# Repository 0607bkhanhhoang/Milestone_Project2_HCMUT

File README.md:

Aquarium Monitoring System Datalogger
Overview
Welcome to the Aquarium Monitoring System Datalogger project! This system is designed to help aquarium enthusiasts and professionals maintain optimal conditions for their aquatic environments by continuously monitoring and logging key parameters.

Features
Real-time Monitoring: Continuously tracks essential water parameters such as temperature, pH, salinity, and dissolved oxygen.
Data Logging: Stores historical data for analysis, helping you identify trends and make informed decisions about your aquarium’s health.
Alerts and Notifications: Sends alerts via email or SMS if any parameter goes out of the safe range, allowing for prompt corrective actions.
User-friendly Interface: Provides a web-based dashboard where users can view real-time data, historical trends, and system status.
Automation Capabilities: Integrates with other smart devices to automate tasks like feeding, lighting, and water changes based on the monitored data.
Components
Sensors: High-precision sensors for measuring temperature, pH, salinity, and dissolved oxygen.
Microcontroller: A microcontroller (e.g., Arduino or Raspberry Pi) to collect data from sensors and send it to the cloud.
Cloud Storage: Secure cloud storage for logging data and providing access from anywhere.
Dashboard: A web-based dashboard built with modern web technologies for data visualization and system management.
Getting Started
Clone the Repository:
git clone https://github.com/yourusername/aquarium-monitoring-system.git
cd aquarium-monitoring-system

Install Dependencies: Follow the instructions in the INSTALL.md file to set up the necessary software and hardware components.
Configure the System: Update the configuration files with your specific settings, such as sensor calibration values and alert thresholds.
Run the System: Start the monitoring system by running the main script:
python main.py

Contributing
We welcome contributions from the community! Please read our CONTRIBUTING.md file for guidelines on how to contribute to this project.

License
This project is licensed under the MIT License. See the LICENSE file for more details.

Feel free to customize this overview to better fit your specific project and its features! If you need more detailed sections or have any other questions, let me know!

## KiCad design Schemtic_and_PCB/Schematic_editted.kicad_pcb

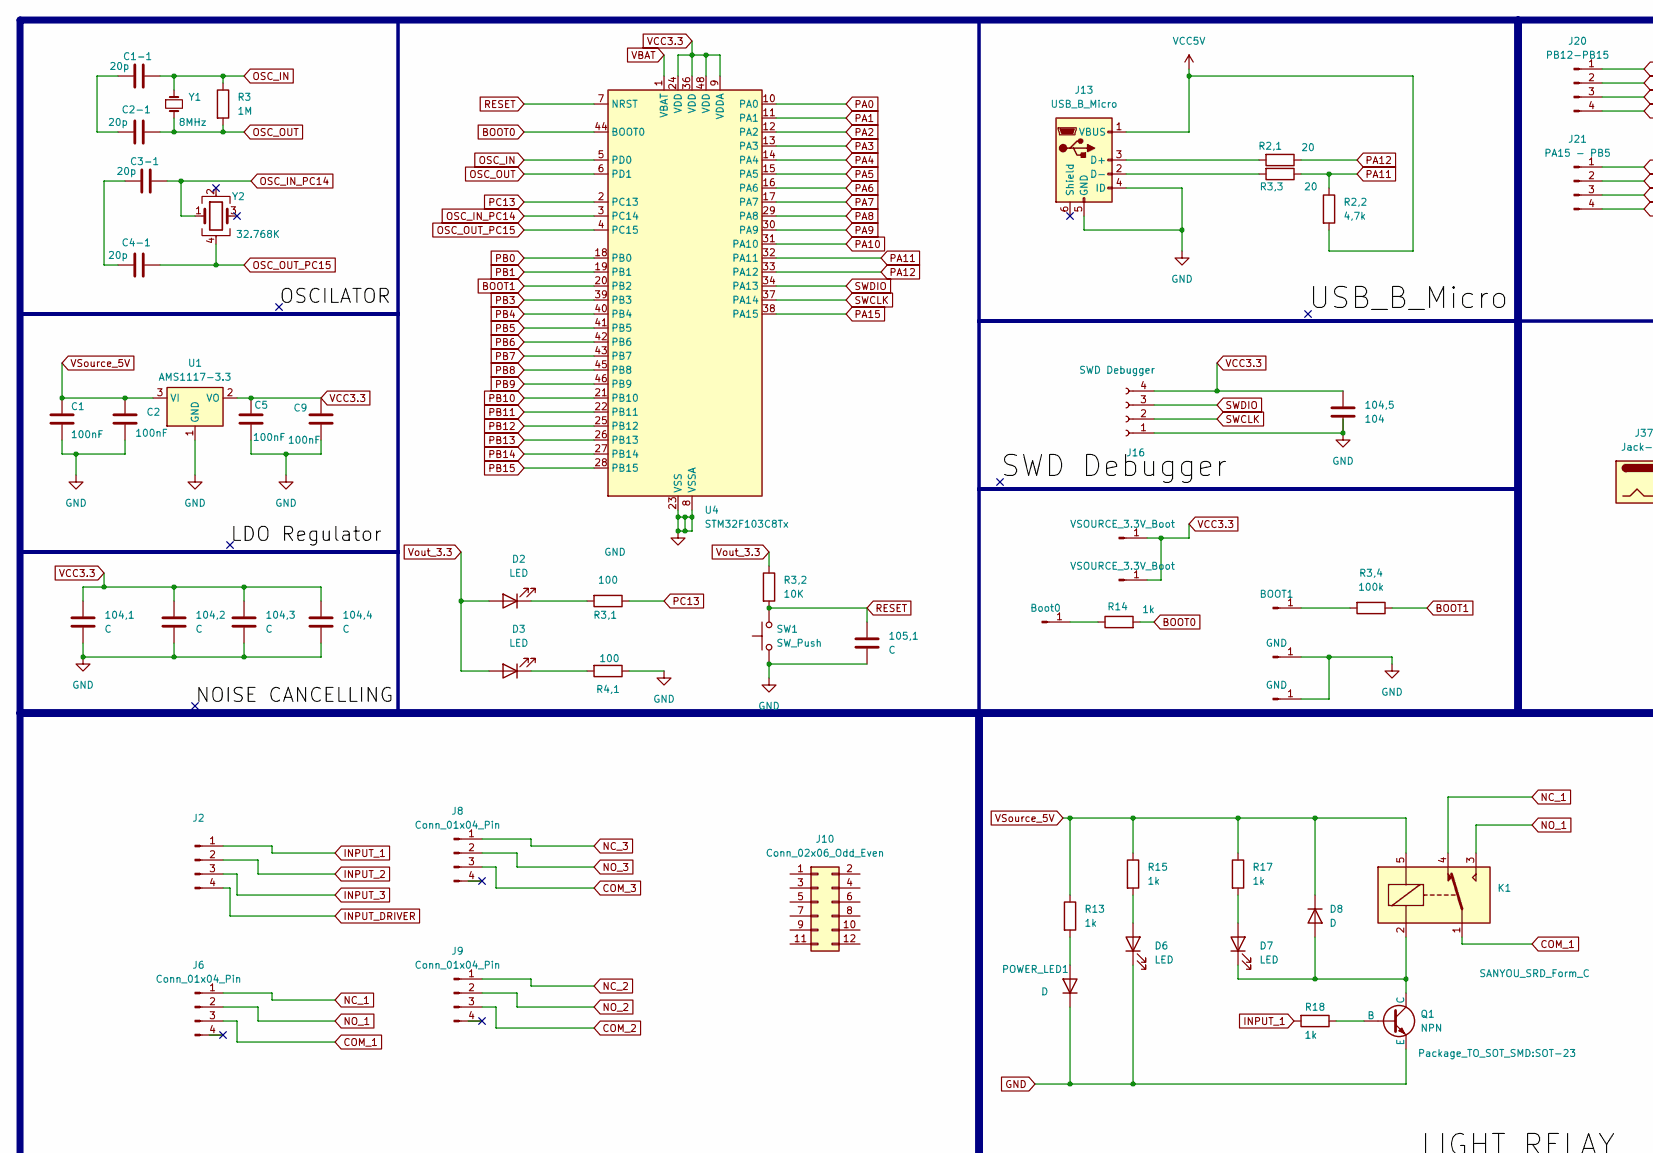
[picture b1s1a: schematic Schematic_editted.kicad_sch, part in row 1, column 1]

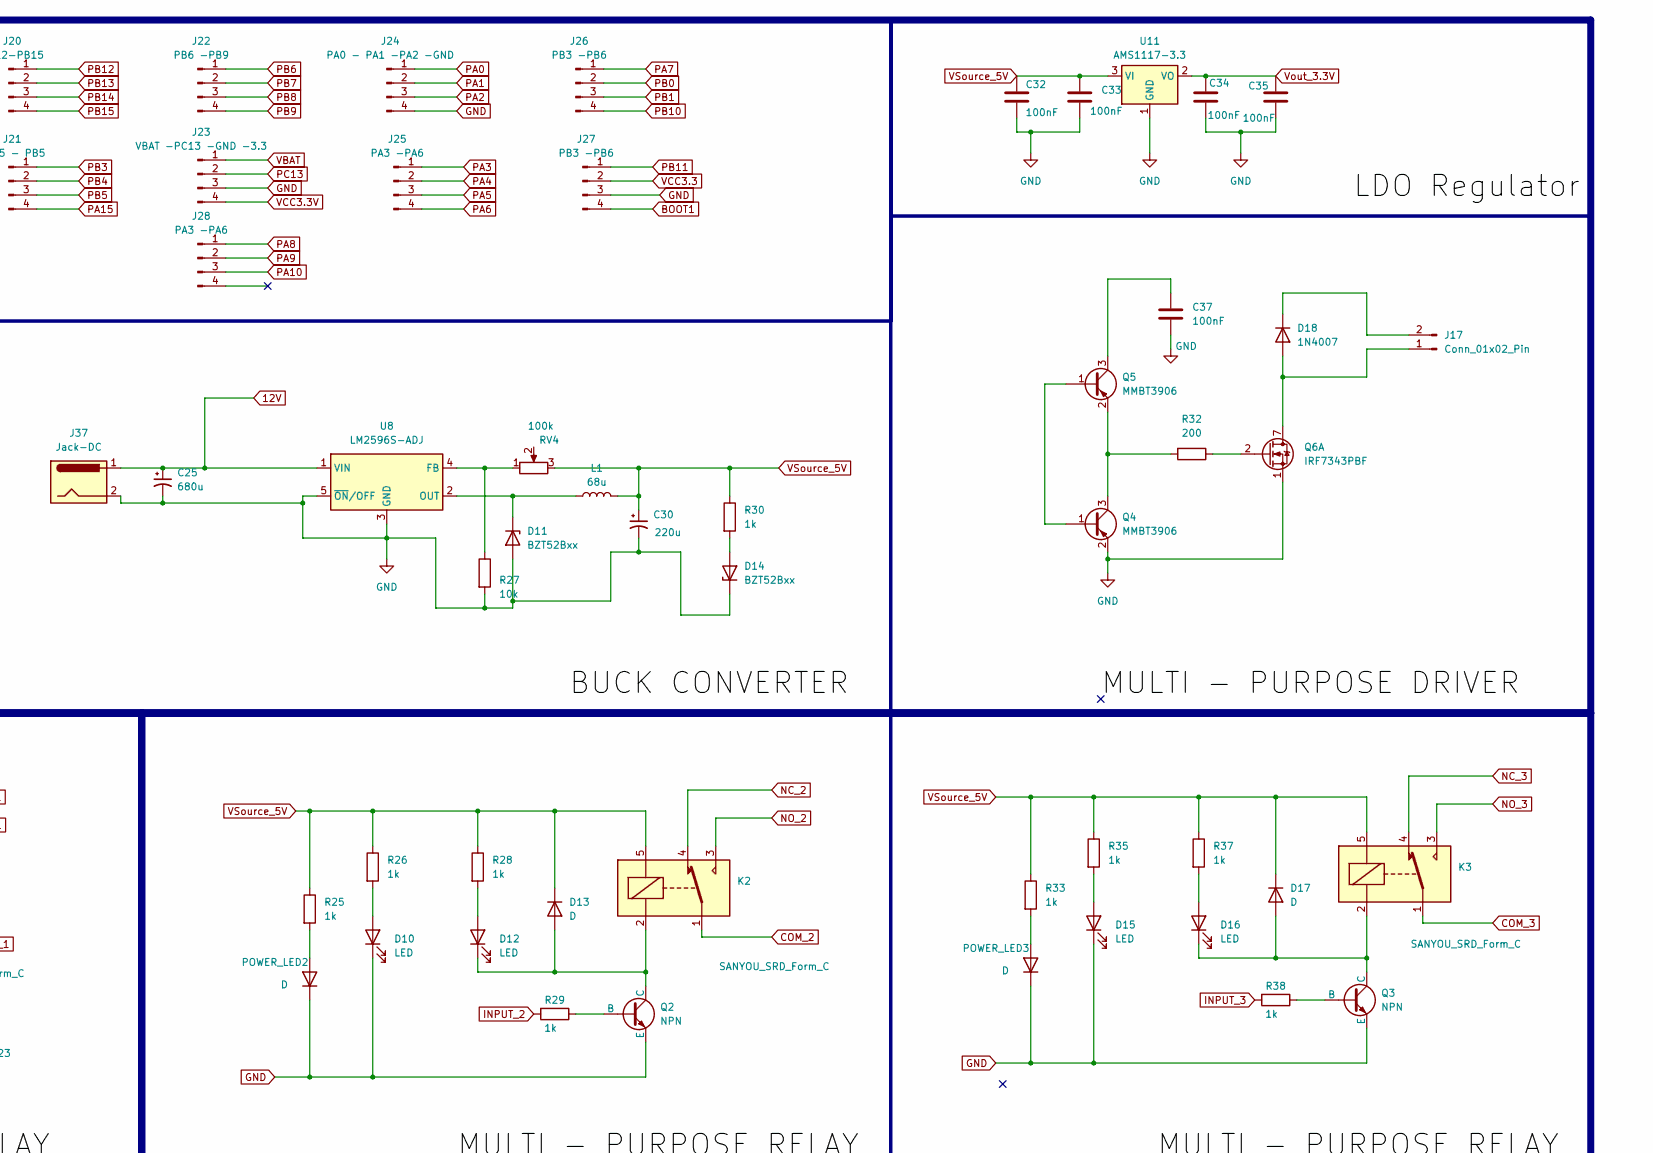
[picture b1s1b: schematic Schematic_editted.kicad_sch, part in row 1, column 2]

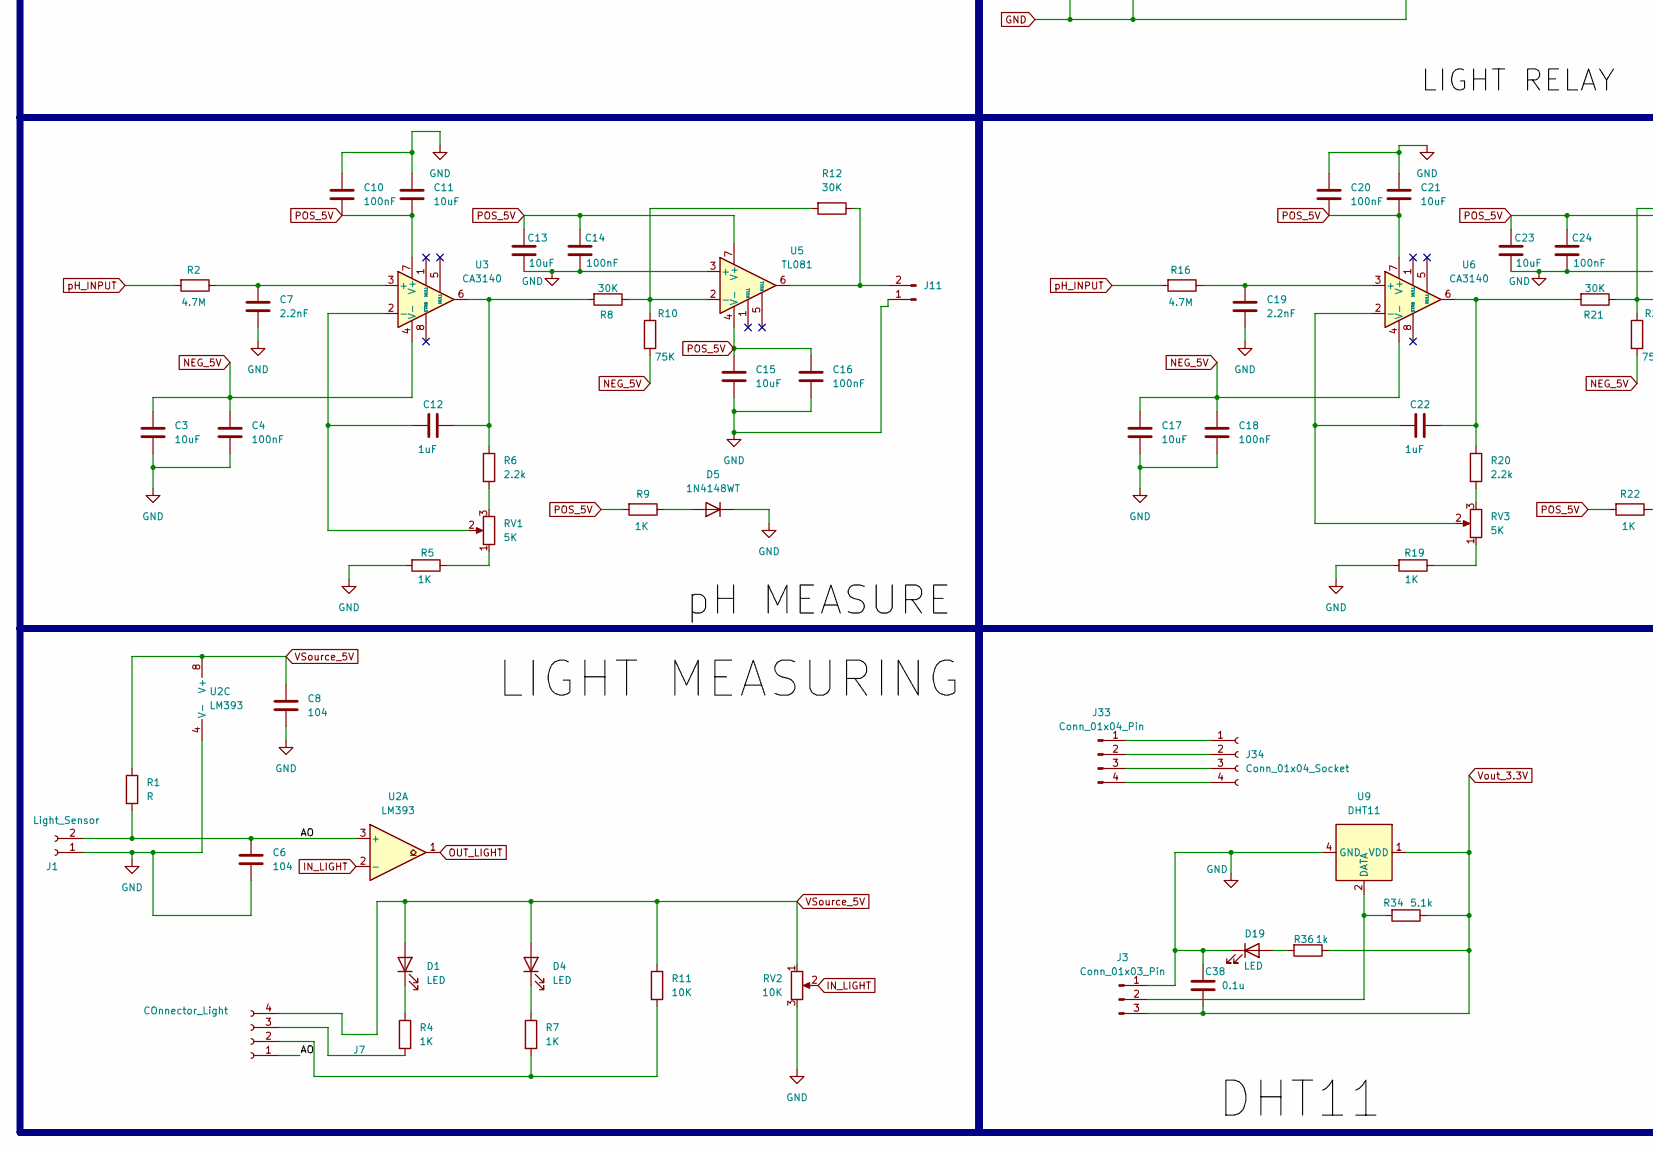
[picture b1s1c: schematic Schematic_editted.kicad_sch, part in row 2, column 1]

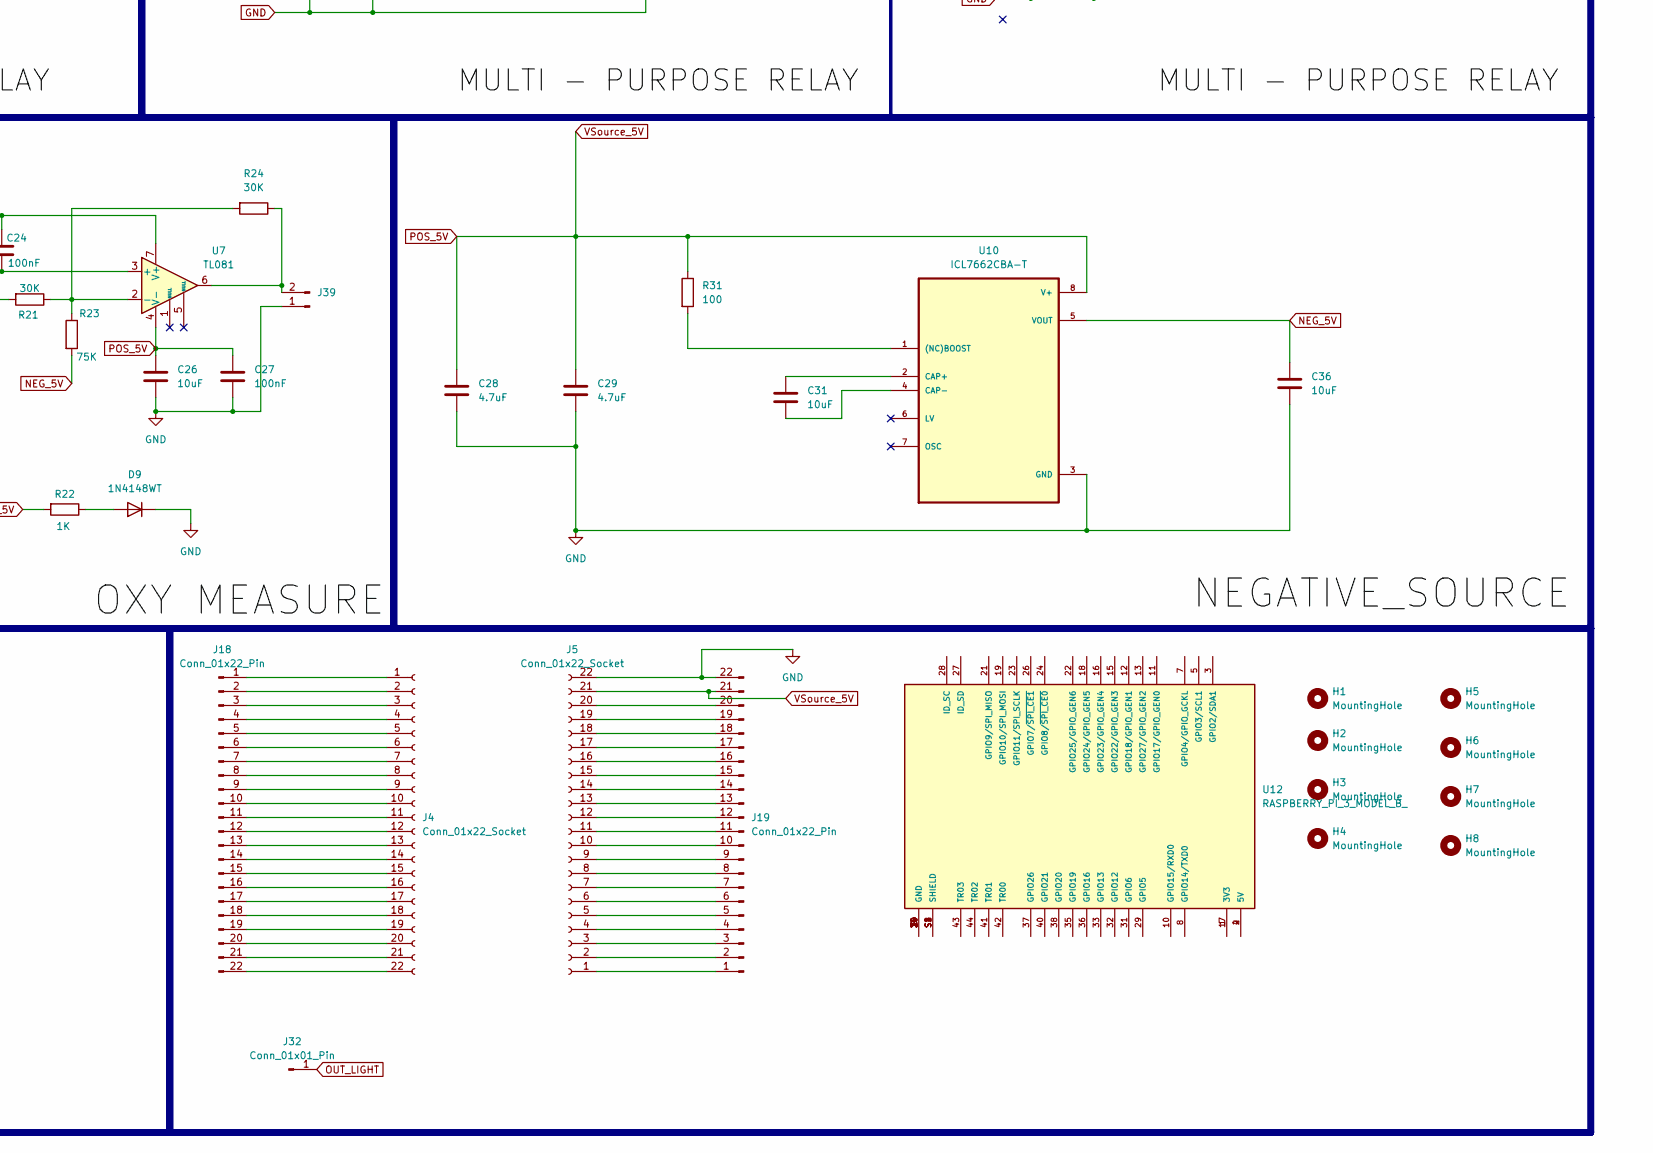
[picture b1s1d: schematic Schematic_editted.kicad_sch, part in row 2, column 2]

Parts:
104,1: C; C_0201_0603Metric
104,2, 105,1: C; C_0603_1608Metric
104,3, 104,4: C; C_0603_1608Metric_Pad1.08x0.95mm_HandSolder
104,5: 104; C_0603_1608Metric
C1, C2, C4, C5, C9, C10, C14, C16, C18, C20, C24, C27, C32, C33, C34, C35, C37: 100nF; C_0603_1608Metric
C1-1, C2-1, C3-1, C4-1: 20p; C_0603_1608Metric
C3, C11, C13, C15, C17, C21, C23, C26, C36: 10uF; C_0603_1608Metric
C6, C8: 104; C_0603_1608Metric
C7, C19: 2.2nF; C_0603_1608Metric
C12, C22: 1uF; C_0603_1608Metric
C25: 680u; CP_Elec_10x10.5
C28: 4.7uF; C_0805_2012Metric_Pad1.18x1.45mm_HandSolder
C29: 4.7uF; C_0805_2012Metric
C30: 220u; CP_Elec_10x10.5
C31: 10uF; C_1206_3216Metric
C38: 0.1u; C_0603_1608Metric
D1, D2: LED; C_0603_1608Metric
D3, D4, D6, D7, D19: LED; LED_0603_1608Metric
D5, D9: 1N4148WT; D_SOD-523
D8: D; LED_0603_1608Metric
D10, D12, D15, D16: LED; LED_0603_1608Metric_Pad1.05x0.95mm_HandSolder
D11, D14: BZT52Bxx; D_SOD-123F
D13, D17: D; LED_0603_1608Metric_Pad1.05x0.95mm_HandSolder
D18: 1N4007; D_DO-41_SOD81_P10.16mm_Horizontal
H1, H2, H3, H4, H5, H6, H7, H8: MountingHole; MountingHole_3.5mm_Pad
J1: Light_Sensor; PinHeader_1x02_P2.00mm_Vertical
J2, J6: Conn_01x04_Pin; PinHeader_1x04_P2.00mm_Vertical_SMD_Pin1Left
J3: Conn_01x03_Pin; PinHeader_1x03_P2.00mm_Vertical
J4, J5: Conn_01x22_Socket; PinHeader_1x22_P2.54mm_Vertical
J7: COnnector_Light; PinSocket_1x05_P2.00mm_Vertical_SMD_Pin1Left
J8, J9: Conn_01x04_Pin; PinSocket_1x05_P2.00mm_Vertical_SMD_Pin1Left
J10: Conn_02x06_Odd_Even
J11, J17, J39: Conn_01x02_Pin; PinHeader_1x02_P2.00mm_Vertical
J12: Boot0; PinHeader_1x01_P2.00mm_Vertical
J13: USB_B_Micro; USB_Micro-B_Wuerth_629105150521_CircularHoles
J14, J15: VSOURCE_3.3V_Boot; PinHeader_1x01_P2.00mm_Vertical
J16: SWD Debugger; PinHeader_1x04_P2.00mm_Vertical
J18, J19: Conn_01x22_Pin; PinSocket_1x22_P2.54mm_Vertical
J20: PB12-PB15; PinHeader_1x04_P2.00mm_Vertical
J21: PA15 - PB5; PinHeader_1x04_P2.00mm_Vertical
J22: PB6 -PB9; PinHeader_1x04_P2.00mm_Vertical
J23: VBAT -PC13 -GND -3.3; PinHeader_1x04_P2.00mm_Vertical
J24: PA0 - PA1 -PA2 -GND; PinHeader_1x04_P2.00mm_Vertical
J25, J28: PA3 -PA6; PinHeader_1x04_P2.00mm_Vertical
J26, J27: PB3 -PB6; PinHeader_1x04_P2.00mm_Vertical
J29: BOOT1; PinHeader_1x01_P2.00mm_Vertical
J30, J31: GND; PinHeader_1x01_P2.00mm_Vertical
J32: Conn_01x01_Pin; PinHeader_1x01_P2.00mm_Vertical
J33: Conn_01x04_Pin; PinHeader_1x04_P2.00mm_Vertical
J34: Conn_01x04_Socket; PinHeader_1x04_P2.00mm_Vertical
J37: Jack-DC; BarrelJack_Horizontal
K1, K2, K3: SANYOU_SRD_Form_C; Relay_SPDT_SANYOU_SRD_Series_Form_C
L1: 68u; L_Walsin_WLFM201609x
POWER_LED1: D; D_0603_1608Metric
POWER_LED2, POWER_LED3: D; D_0201_0603Metric
Q1, Q2, Q3: NPN; SOT-23
Q4, Q5: MMBT3906; SOT-23
Q6: IRF7343PBF; SOIC-8_3.9x4.9mm_P1.27mm
R1: R; R_0603_1608Metric_Pad0.98x0.95mm_HandSolder
R2, R16: 4.7M; R_0603_1608Metric_Pad0.98x0.95mm_HandSolder
R2,1, R3,3: 20; R_0603_1608Metric_Pad0.98x0.95mm_HandSolder
R2,2: 4,7k; R_0603_1608Metric_Pad0.98x0.95mm_HandSolder
R3: 1M; R_0603_1608Metric_Pad0.98x0.95mm_HandSolder
R3,1, R4,1: 100; R_0603_1608Metric_Pad0.98x0.95mm_HandSolder
R3,2, R11: 10K; R_0603_1608Metric_Pad0.98x0.95mm_HandSolder
R3,4: 100k; R_0603_1608Metric_Pad0.98x0.95mm_HandSolder
R4, R5, R7, R9, R19, R22: 1K; R_0603_1608Metric_Pad0.98x0.95mm_HandSolder
R6, R20: 2.2k; R_0603_1608Metric_Pad0.98x0.95mm_HandSolder
R8, R12, R21, R24: 30K; R_0603_1608Metric_Pad0.98x0.95mm_HandSolder
R10, R23: 75K; R_0603_1608Metric_Pad0.98x0.95mm_HandSolder
R13, R14, R15, R17, R18, R25, R26, R28, R29, R30, R33, R35, R37, R38: 1k; R_0603_1608Metric_Pad0.98x0.95mm_HandSolder
R27: 10k; R_0603_1608Metric
R31: 100; R_0603_1608Metric
R32: 200; R_0603_1608Metric
R34: 5.1k; R_0603_1608Metric
R36: 1k; R_0603_1608Metric
RV1, RV3: 5K; R_0603_1608Metric_Pad0.98x0.95mm_HandSolder
RV2: 10K; R_0603_1608Metric_Pad0.98x0.95mm_HandSolder
RV4: 100k; Potentiometer_Bourns_3266Y_Vertical
SW1: SW_Push; LED_0603_1608Metric
U1, U11: AMS1117-3.3; SOT-223-3_TabPin2
U2: LM393; VSSOP-8_3x3mm_P0.65mm
U3, U6: CA3140; SOIC-8-1EP_3.9x4.9mm_P1.27mm_EP2.29x3mm_ThermalVias
U4: STM32F103C8Tx; LQFP-48_7x7mm_P0.5mm
U5: TL081; SOIC-8-1EP_3.9x4.9mm_P1.27mm_EP2.41x3.81mm_ThermalVias
U7: TL081; SOIC-8-1EP_3.9x4.9mm_P1.27mm_EP2.29x3mm_ThermalVias
U8: LM2596S-ADJ; TO-263-5_TabPin3
U9: DHT11; Aosong_DHT11_5.5x12.0_P2.54mm
U10: ICL7662CBA-T; SOIC-8-1EP_3.9x4.9mm_P1.27mm_EP2.62x3.51mm
U12: RASPBERRY_PI_3_MODEL_B_; MODULE_RASPBERRY_PI_3_MODEL_B_; PARTREV N/A
Y1: 8MHz; Crystal_HC52-U_Vertical
Y2: 32.768K; Crystal_SMD_SeikoEpson_MC306-4Pin_8.0x3.2mm_HandSoldering

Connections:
12V: C25.1, J37.1, U8.1 (VIN)
/AO: C6.1, J1.2, J7.1, R1.2, U2.3 (+)
BOOT0: R14.2, U4.44 (BOOT0)
BOOT1: J27.4, R3,4.1, U4.20 (PB2)
COM_1: J6.3, K1.1
COM_2: J9.3, K2.1
COM_3: J8.3, K3.1
GND: 104,1.2, 104,2.2, 104,3.2, 104,4.2, 104,5.2, 105,1.2, C1.2, C2.2, C3.2, C4.2, C5.2, C6.2, C7.2, C8.2, C9.2, C10.1, C11.1, C13.2, C14.2, C15.2, C16.2, C17.2, C18.2, C19.2, C20.1, C21.1, C23.2, C24.2, C25.2, C26.2, C27.2, C28.2, C29.2, C30.2, C32.2, C33.2, C34.2, C35.2, C36.2, C37.2, C38.1, D5.1 (K), D6.1 (K), D9.1 (K), D10.1 (K), D11.2 (A), D14.1 (K), D15.1 (K), D19.1 (K), J1.1, J3.1, J5.22, J11.1, J13.4 (ID), J13.5 (GND), J16.1, J19.22, J23.3, J24.4, J27.3, J30.1, J31.1, J37.2, J39.1, POWER_LED1.1 (K), POWER_LED2.1 (K), POWER_LED3.1 (K), Q1.3 (E), Q2.3 (E), Q3.3 (E), Q4.2 (E), Q6.1 (S), R4,1.1, R5.2, R19.2, R27.2, RV2.3, SW1.1, U1.1 (GND), U2.4 (V-), U4.8 (VSSA), U4.23 (VSS), U4.35 (VSS), U4.47 (VSS), U5.3 (+), U7.3 (+), U8.3 (GND), U8.5 (~ON/OFF), U9.4 (GND), U10.3 (GND), U11.1 (GND)
INPUT_1: J2.1, R18.2
INPUT_2: J2.2, R29.2
INPUT_3: J2.3, R38.2
INPUT_DRIVER: J2.4
IN_LIGHT: RV2.2, U2.2 (-)
NC_1: J6.1, K1.4
NC_2: J9.1, K2.4
NC_3: J8.1, K3.4
NEG_5V: C3.1, C4.1, C17.1, C18.1, C36.1, R10.2, R23.2, U3.4 (V-), U6.4 (V-), U10.5 (VOUT)
NO_1: J6.2, K1.3
NO_2: J9.2, K2.3
NO_3: J8.2, K3.3
unnamed: C1-1.2, C2-1.2
unnamed: C3-1.2, C4-1.2
unnamed: C12.1, R6.1, R8.2, U3.6
unnamed: C22.1, R20.1, R21.2, U6.6
unnamed: D1.1 (K), R4.1
unnamed: D2.1 (K), R3,1.2
unnamed: D3.1 (K), R4,1.2
unnamed: D4.1 (K), R7.1
unnamed: D5.2 (A), R9.1
unnamed: D6.2 (A), R15.2
unnamed: D7.2 (A), R17.2
unnamed: D7.1 (K), D8.2 (A), K1.2, Q1.1 (C)
unnamed: D9.2 (A), R22.1
unnamed: D10.2 (A), R26.2
unnamed: D11.1 (K), L1.1, U8.2 (OUT)
unnamed: D12.2 (A), R28.2
unnamed: D12.1 (K), D13.2 (A), K2.2, Q2.1 (C)
unnamed: D14.2 (A), R30.2
unnamed: D15.2 (A), R35.2
unnamed: D16.2 (A), R37.2
unnamed: D16.1 (K), D17.2 (A), K3.2, Q3.1 (C)
unnamed: D18.2 (A), J17.1, Q6.7 (D), Q6.8 (D)
unnamed: D18.1 (K), J17.2
unnamed: D19.2 (A), R36.2
unnamed: J3.2, R34.2, U9.2 (DATA)
unnamed: J7.2, R7.2, R11.2
unnamed: J7.3, R4.2
unnamed: J11.2, R12.1, U5.6
unnamed: J12.1, R14.1
unnamed: J13.3 (D+), R2,1.2
unnamed: J13.2 (D-), R3,3.2
unnamed: J4.1, J18.1
unnamed: J4.2, J18.2
unnamed: J4.3, J18.3
unnamed: J4.4, J18.4
unnamed: J4.5, J18.5
unnamed: J4.6, J18.6
unnamed: J4.7, J18.7
unnamed: J4.8, J18.8
unnamed: J4.9, J18.9
unnamed: J4.10, J18.10
unnamed: J4.11, J18.11
unnamed: J4.12, J18.12
unnamed: J4.13, J18.13
unnamed: J4.14, J18.14
unnamed: J4.15, J18.15
unnamed: J4.16, J18.16
unnamed: J4.17, J18.17
unnamed: J4.18, J18.18
unnamed: J4.19, J18.19
unnamed: J4.20, J18.20
unnamed: J4.21, J18.21
unnamed: J4.22, J18.22
unnamed: J5.1, J19.1
unnamed: J5.2, J19.2
unnamed: J5.3, J19.3
unnamed: J5.4, J19.4
unnamed: J5.5, J19.5
unnamed: J5.6, J19.6
unnamed: J5.7, J19.7
unnamed: J5.8, J19.8
unnamed: J5.9, J19.9
unnamed: J5.10, J19.10
unnamed: J5.11, J19.11
unnamed: J5.12, J19.12
unnamed: J5.13, J19.13
unnamed: J5.14, J19.14
unnamed: J5.15, J19.15
unnamed: J5.16, J19.16
unnamed: J5.17, J19.17
unnamed: J5.18, J19.18
unnamed: J5.19, J19.19
unnamed: J5.20, J19.20
unnamed: J29.1, R3,4.2
unnamed: J33.1, J34.1
unnamed: J33.2, J34.2
unnamed: J33.3, J34.3
unnamed: J33.4, J34.4
unnamed 98: J39.2, R24.1, U7.6; also elsewhere on the board
unnamed: POWER_LED1.2 (A), R13.2
unnamed: POWER_LED2.2 (A), R25.2
unnamed: POWER_LED3.2 (A), R33.2
unnamed: Q1.2 (B), R18.1
unnamed: Q2.2 (B), R29.1
unnamed: Q3.2 (B), R38.1
unnamed: Q4.1 (B), Q5.1 (B)
unnamed: Q4.3 (C), Q5.2 (E), R32.2
unnamed: C37.1, Q5.3 (C)
unnamed: Q6.2 (G), R32.1
unnamed: R5.1, RV1.1
unnamed: R6.2, RV1.3
unnamed: R19.1, RV3.1
unnamed: R20.2, RV3.3
unnamed: C7.1, R2.1, U3.3 (+)
unnamed: C12.2, RV1.2, U3.2 (-)
unnamed: R8.1, R10.1, R12.2, U5.2 (-)
unnamed: C19.1, R16.1, U6.3 (+)
unnamed: C22.2, RV3.2, U6.2 (-)
unnamed: R21.1, R23.1, R24.2, U7.2 (-)
unnamed: R27.1, RV4.1, U8.4 (FB)
unnamed: R31.2, U10.1 ((NC)BOOST)
unnamed: C31.1, U10.2 (CAP+)
unnamed: C31.2, U10.4 (CAP-)
unnamed: U12.1 (3V3), U12.17 (3V3)
unnamed: U12.2 (5V), U12.4 (5V)
unnamed: U12.6 (GND), U12.9 (GND), U12.14 (GND), U12.20 (GND), U12.25 (GND), U12.30 (GND), U12.34 (GND), U12.39 (GND)
unnamed: U12.S1 (SHIELD), U12.S2 (SHIELD), U12.S3 (SHIELD), U12.S4 (SHIELD)
OSC_IN: C1-1.1, R3.1, U4.5 (PD0), Y1.1
OSC_IN_PC14: C3-1.1, U4.3 (PC14), Y2.1
OSC_OUT: C2-1.1, R3.2, U4.6 (PD1), Y1.2
OSC_OUT_PC15: C4-1.1, U4.4 (PC15), Y2.4
OUT_LIGHT: J32.1, U2.1
PA0: J24.1, U4.10 (PA0)
PA1: J24.2, U4.11 (PA1)
PA2: J24.3, U4.12 (PA2)
PA3: J25.1, U4.13 (PA3)
PA4: J25.2, U4.14 (PA4)
PA5: J25.3, U4.15 (PA5)
PA6: J25.4, U4.16 (PA6)
PA7: J26.1, U4.17 (PA7)
PA8: J28.1, U4.29 (PA8)
PA9: J28.2, U4.30 (PA9)
PA10: J28.3, U4.31 (PA10)
PA11: R2,2.1, R3,3.1, U4.32 (PA11)
PA12: R2,1.1, U4.33 (PA12)
PA15: J21.4, U4.38 (PA15)
PB0: J26.2, U4.18 (PB0)
PB1: J26.3, U4.19 (PB1)
PB3: J21.1, U4.39 (PB3)
PB4: J21.2, U4.40 (PB4)
PB5: J21.3, U4.41 (PB5)
PB6: J22.1, U4.42 (PB6)
PB7: J22.2, U4.43 (PB7)
PB8: J22.3, U4.45 (PB8)
PB9: J22.4, U4.46 (PB9)
PB10: J26.4, U4.21 (PB10)
PB11: J27.1, U4.22 (PB11)
PB12: J20.1, U4.25 (PB12)
PB13: J20.2, U4.26 (PB13)
PB14: J20.3, U4.27 (PB14)
PB15: J20.4, U4.28 (PB15)
PC13: J23.2, R3,1.1, U4.2 (PC13)
POS_5V: C1.1, C2.1, C8.1, C10.2, C11.2, C13.1, C14.1, C15.1, C16.1, C20.2, C21.2, C23.1, C24.1, C26.1, C27.1, C28.1, C29.1, C30.1, C32.1, C33.1, D1.2 (A), D4.2 (A), D8.1 (K), D13.1 (K), D17.1 (K), J5.21, J7.4, J19.21, K1.5, K2.5, K3.5, L1.2, R1.1, R9.2, R11.1, R13.1, R15.1, R17.1, R22.2, R25.1, R26.1, R28.1, R30.1, R31.1, R33.1, R35.1, R37.1, RV2.1, RV4.3, U1.3 (VI), U2.8 (V+), U3.7 (V+), U5.4 (V-), U5.7 (V+), U6.7 (V+), U7.4 (V-), U7.7 (V+), U10.8 (V+), U11.3 (VI); also elsewhere on the board
RESET: 105,1.1, R3,2.2, SW1.2, U4.7 (NRST)
SWCLK: J16.2, U4.37 (PA14)
SWDIO: J16.3, U4.34 (PA13)
VBAT: J23.1, U4.1 (VBAT)
VCC3.3: 104,1.1, 104,2.1, 104,3.1, 104,4.1, 104,5.1, C5.1, C9.1, J14.1, J15.1, J16.4, J27.2, U1.2 (VO), U4.9 (VDDA), U4.24 (VDD), U4.36 (VDD), U4.48 (VDD)
VCC3.3V: J23.4
VCC5V: J13.1 (VBUS), R2,2.2
Vout_3.3: D2.2 (A), D3.2 (A), R3,2.1
Vout_3.3V: C34.1, C35.1, C38.2, J3.3, R34.1, R36.1, U9.1 (VDD), U11.2 (VO)
pH_INPUT: R2.2, R16.2

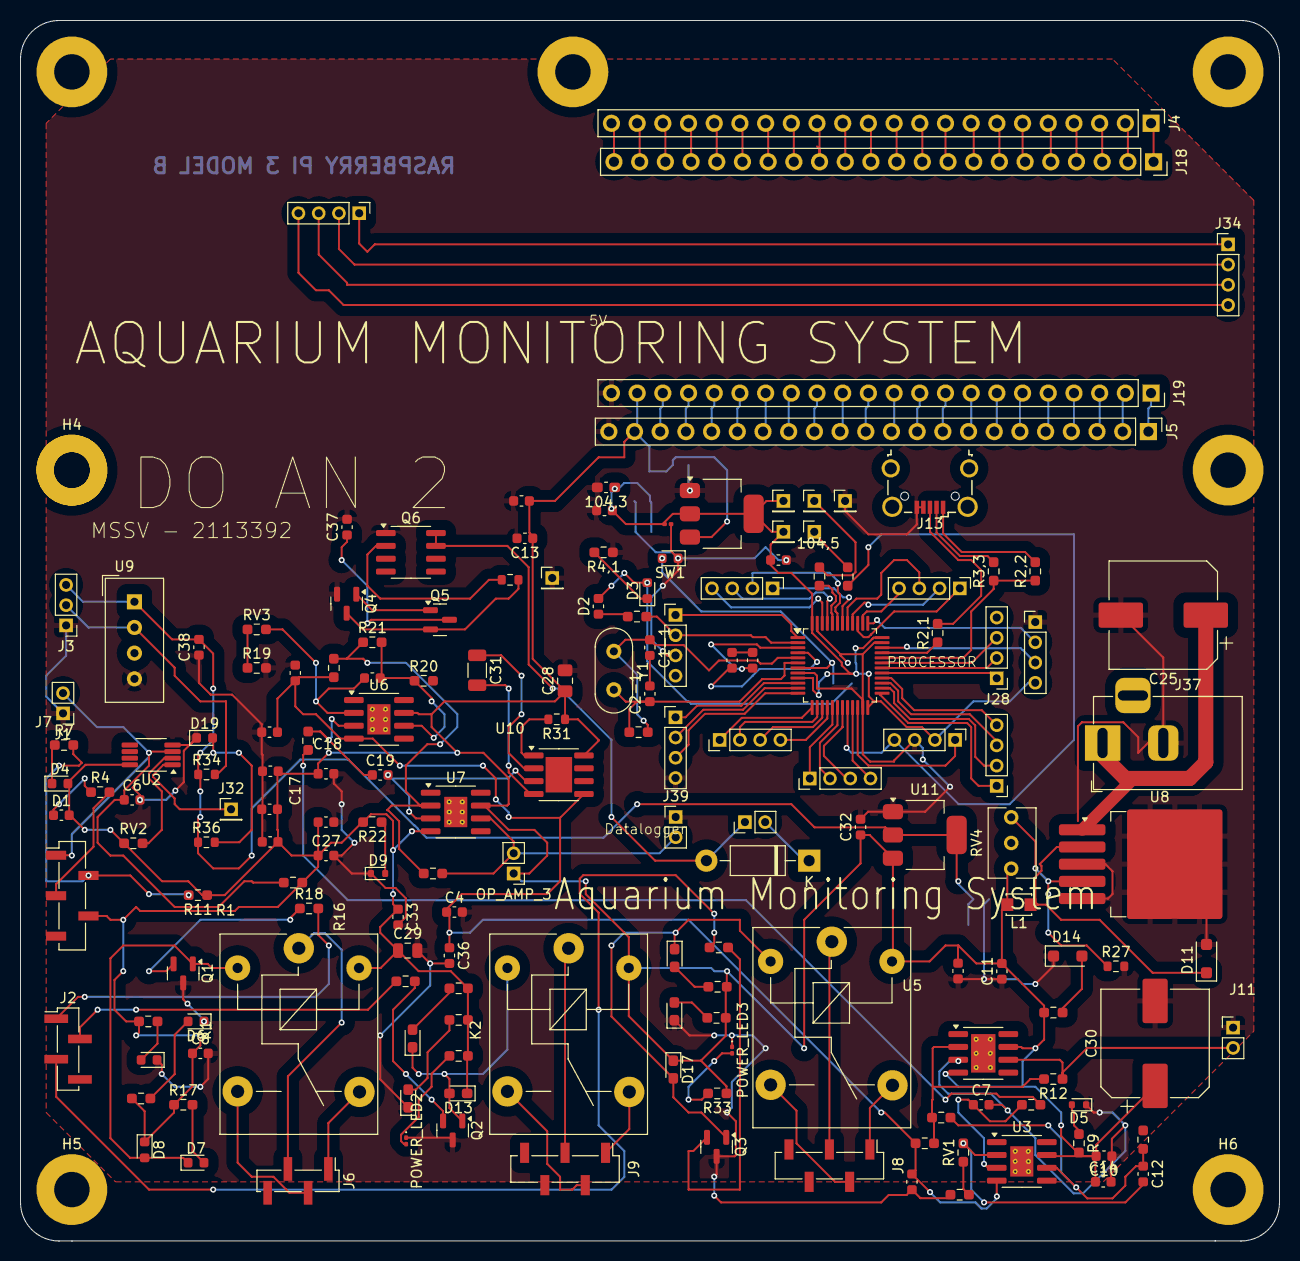
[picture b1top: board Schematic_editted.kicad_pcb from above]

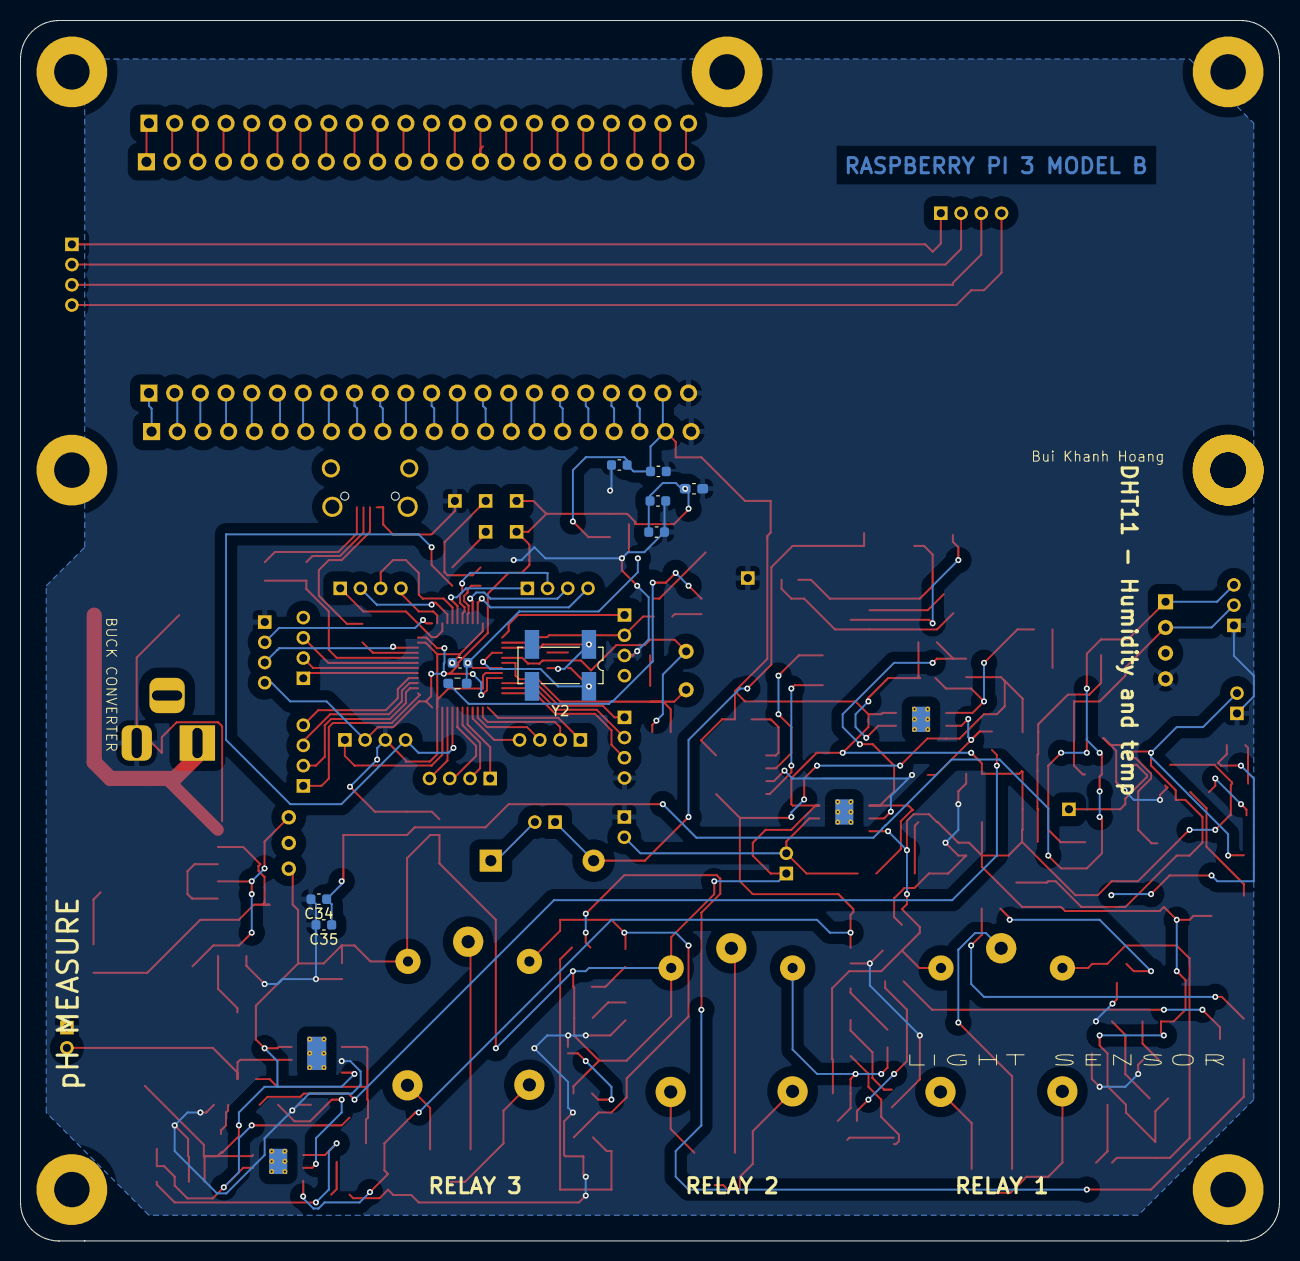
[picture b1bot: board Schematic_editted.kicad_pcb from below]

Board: 2 copper layers, 124.5 x 120.7 mm, 187 parts (10 on the bottom side), 165 nets.

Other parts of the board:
OP_AMP_3: Conn_01x02_Pin; PinHeader_1x02_P2.00mm_Vertical

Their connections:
unnamed 98: OP_AMP_3.2; also elsewhere on the board
POS_5V: OP_AMP_3.1; also elsewhere on the board

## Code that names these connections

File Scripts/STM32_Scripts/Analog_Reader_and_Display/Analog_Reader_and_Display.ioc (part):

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Mcu.Name=STM32F103C(8-B)Tx
Mcu.Package=LQFP48
Mcu.UserName=STM32F103C8Tx
PA0-WKUP.Signal=ADCx_IN0
PA1.Signal=ADCx_IN1
PA10.Mode=Asynchronous
PA10.Signal=USART1_RX
PA13.Mode=Serial_Wire
PA13.Signal=SYS_JTMS-SWDIO
PA14.Mode=Serial_Wire
PA14.Signal=SYS_JTCK-SWCLK
PA2.Signal=ADCx_IN2
PA3.Signal=GPIO_Output
PA5.Signal=GPIO_Output
PA6.Signal=GPIO_Output
PA7.Signal=GPIO_Output
PA8.Signal=S_TIM1_CH1
PA9.Mode=Asynchronous
PA9.Signal=USART1_TX
PB6.Mode=I2C
PB6.Signal=I2C1_SCL
PB7.Mode=I2C
PB7.Signal=I2C1_SDA
PC14-OSC32_IN.Mode=LSE-External-Oscillator
PC14-OSC32_IN.Signal=RCC_OSC32_IN
PC15-OSC32_OUT.Mode=LSE-External-Oscillator
PC15-OSC32_OUT.Signal=RCC_OSC32_OUT
PD0-OSC_IN.Mode=HSE-External-Oscillator
PD0-OSC_IN.Signal=RCC_OSC_IN
PD1-OSC_OUT.Mode=HSE-External-Oscillator
PD1-OSC_OUT.Signal=RCC_OSC_OUT
RCC.HSEDivPLL=RCC_HSE_PREDIV_DIV2
RCC.SYSCLKFreq_VALUE=48000000
RCC.SYSCLKSource=RCC_SYSCLKSOURCE_PLLCLK
board=custom

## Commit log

2024-10-14 added sch pcb
2024-10-16 ADd stm32
